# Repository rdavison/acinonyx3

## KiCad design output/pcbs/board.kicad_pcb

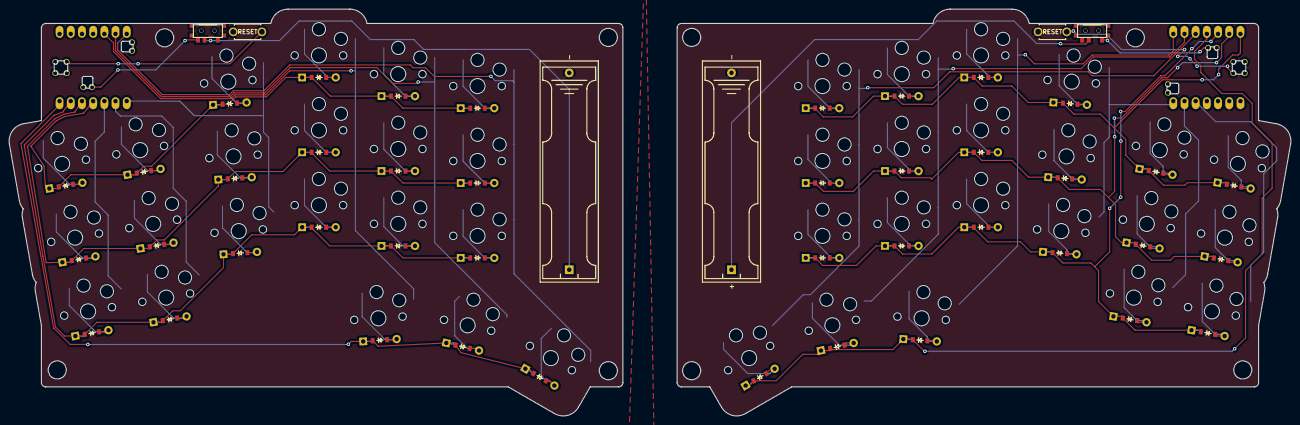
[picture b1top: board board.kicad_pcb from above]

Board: 2 copper layers, 290.9 x 92.3 mm, 92 parts (0 on the bottom side), 70 nets.

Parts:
AAAL: BatteryHolder_Keystone_2466_1xAAA
AAAR: BatteryHolder_Keystone_2466_1xAAA
B1, B2: ResetSW
D1, D2, D3, D4, D5, D6, D7, D8, D9, D10, D11, D12, D13, D14, D15, D16, D17, D18, D19, D20, D21, D22, D23, D24, D25, D26, D27, D28, D29, D30, D31, D32, D33, D34, D35, D36, D37, D38, D39, D40, D41, D42: ComboDiode
MCU1, MCU2: xiao-ble; XIAO-BLE
S1, S2, S3, S4, S5, S6, S7, S8, S9, S10, S11, S12, S13, S14, S15, S16, S17, S18, S19, S20, S21, S22, S23, S24, S25, S26, S27, S28, S29, S30, S31, S32, S33, S34, S35, S36, S37, S38, S39, S40, S41, S42: PG1350
T1, T2: SPDT_C128955

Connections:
BAT_POS: MCU1.19, T1.3
GND: AAAL.2, B1.2, MCU1.13, MCU1.17
RAW: AAAL.1, T1.2
RST: B1.1, MCU1.18
col_index: MCU1.9, S13.2, S14.2, S15.2, S20.2
col_inner: MCU1.8, S16.2, S17.2, S18.2, S21.2
col_middle: MCU1.10, S10.2, S11.2, S12.2, S19.2
col_outer: MCU1.5, S1.2, S2.2, S3.2
col_pinky: MCU1.6, S4.2, S5.2, S6.2
col_ring: MCU1.7, S7.2, S8.2, S9.2
far_thumb: D21.2, S21.1
home_thumb: D20.2, S20.1
index_bottom: D13.2, S13.1
index_home: D14.2, S14.1
index_top: D15.2, S15.1
inner_bottom: D16.2, S16.1
inner_home: D17.2, S17.1
inner_top: D18.2, S18.1
middle_bottom: D10.2, S10.1
middle_home: D11.2, S11.1
middle_top: D12.2, S12.1
mirror_BAT_POS: MCU2.19, T2.1
mirror_GND: AAAR.2, B2.2, MCU2.13, MCU2.17
mirror_RAW: AAAR.1, T2.2
mirror_RST: B2.1, MCU2.18
mirror_col_index: MCU2.6, S34.2, S35.2, S36.2, S41.2
mirror_col_inner: MCU2.5, S37.2, S38.2, S39.2, S42.2
mirror_col_middle: MCU2.7, S31.2, S32.2, S33.2, S40.2
mirror_col_outer: MCU2.10, S22.2, S23.2, S24.2
mirror_col_pinky: MCU2.9, S25.2, S26.2, S27.2
mirror_col_ring: MCU2.8, S28.2, S29.2, S30.2
mirror_far_thumb: D42.2, S42.1
mirror_home_thumb: D41.2, S41.1
mirror_index_bottom: D34.2, S34.1
mirror_index_home: D35.2, S35.1
mirror_index_top: D36.2, S36.1
mirror_inner_bottom: D37.2, S37.1
mirror_inner_home: D38.2, S38.1
mirror_inner_top: D39.2, S39.1
mirror_middle_bottom: D31.2, S31.1
mirror_middle_home: D32.2, S32.1
mirror_middle_top: D33.2, S33.1
mirror_near_thumb: D40.2, S40.1
mirror_outer_bottom: D22.2, S22.1
mirror_outer_home: D23.2, S23.1
mirror_outer_top: D24.2, S24.1
mirror_pinky_bottom: D25.2, S25.1
mirror_pinky_home: D26.2, S26.1
mirror_pinky_top: D27.2, S27.1
mirror_ring_bottom: D28.2, S28.1
mirror_ring_home: D29.2, S29.1
mirror_ring_top: D30.2, S30.1
mirror_row_bottom: D22.1, D25.1, D28.1, D31.1, D34.1, D37.1, MCU2.3
mirror_row_home: D23.1, D26.1, D29.1, D32.1, D35.1, D38.1, MCU2.2
mirror_row_thumb: D40.1, D41.1, D42.1, MCU2.4
mirror_row_top: D24.1, D27.1, D30.1, D33.1, D36.1, D39.1, MCU2.1
near_thumb: D19.2, S19.1
outer_bottom: D1.2, S1.1
outer_home: D2.2, S2.1
outer_top: D3.2, S3.1
pinky_bottom: D4.2, S4.1
pinky_home: D5.2, S5.1
pinky_top: D6.2, S6.1
ring_bottom: D7.2, S7.1
ring_home: D8.2, S8.1
ring_top: D9.2, S9.1
row_bottom: D1.1, D4.1, D7.1, D10.1, D13.1, D16.1, MCU1.2
row_home: D2.1, D5.1, D8.1, D11.1, D14.1, D17.1, MCU1.3
row_thumb: D19.1, D20.1, D21.1, MCU1.1
row_top: D3.1, D6.1, D9.1, D12.1, D15.1, D18.1, MCU1.4

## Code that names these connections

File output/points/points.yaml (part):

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                pinky: &ref_2
                    key:
                        stagger: 0 ky
                        column_net: col_pinky
                        mirror:
                            column_net: mirror_col_pinky
                    rows: {}
                    name: pinky
                ring: &ref_3
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        autobind: 10
        skip: false
        asym: both
        colrow: pinky_bottom
        name: matrix_pinky_bottom
        column_net: col_pinky
        mirror:
            column_net: mirror_col_pinky
            row_net: mirror_row_bottom
        row_net: row_bottom
        zone: *ref_1
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        autobind: 10
        skip: false
        asym: both
        colrow: pinky_home
        name: matrix_pinky_home
        column_net: col_pinky
        mirror:
            column_net: mirror_col_pinky
            row_net: mirror_row_home
        row_net: row_home
        zone: *ref_1
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        autobind: 10
        skip: false
        asym: both
        colrow: pinky_top
        name: matrix_pinky_top
        column_net: col_pinky
        mirror:
            column_net: mirror_col_pinky
            row_net: mirror_row_top
        row_net: row_top
        zone: *ref_1
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                pinky:
                    key:
                        stagger: 0 ky
                        column_net: col_pinky
                        mirror:
                            column_net: mirror_col_pinky
                    rows: {}
                    name: pinky
                ring:
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                pinky:
                    key:
                        stagger: 0 ky
                        column_net: col_pinky
                        mirror:
                            column_net: mirror_col_pinky
                    rows: {}
                    name: pinky
                ring:
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                pinky:
                    key:
                        stagger: 0 ky
                        column_net: col_pinky
                        mirror:
                            column_net: mirror_col_pinky
                    rows: {}
                    name: pinky
                ring:
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        autobind: 10
        skip: false
        asym: both
        colrow: mirror_pinky_bottom
        name: mirror_matrix_pinky_bottom
        column_net: mirror_col_pinky
        mirror:
            column_net: mirror_col_pinky
            row_net: mirror_row_bottom
        row_net: mirror_row_bottom
        zone:
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                pinky:
                    key:
                        stagger: 0 ky
                        column_net: col_pinky
                        mirror:
                            column_net: mirror_col_pinky
                    rows: {}
                    name: pinky
                ring:
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        col:
            key:
                stagger: 0 ky
                column_net: col_pinky
                mirror:
                    column_net: mirror_col_pinky
            rows: {}
            name: pinky
        row: bottom
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        autobind: 10
        skip: false
        asym: both
        colrow: mirror_pinky_home
        name: mirror_matrix_pinky_home
        column_net: mirror_col_pinky
        mirror:
            column_net: mirror_col_pinky
            row_net: mirror_row_home
        row_net: mirror_row_home
        zone:
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                pinky:
                    key:
                        stagger: 0 ky
                        column_net: col_pinky
                        mirror:
                            column_net: mirror_col_pinky
                    rows: {}
                    name: pinky
                ring:
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        col:
            key:
                stagger: 0 ky
                column_net: col_pinky
                mirror:
                    column_net: mirror_col_pinky
            rows: {}
            name: pinky
        row: home
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        autobind: 10
        skip: false
        asym: both
        colrow: mirror_pinky_top
        name: mirror_matrix_pinky_top
        column_net: mirror_col_pinky
        mirror:
            column_net: mirror_col_pinky
            row_net: mirror_row_top
        row_net: mirror_row_top
        zone:
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                pinky:
                    key:
                        stagger: 0 ky
                        column_net: col_pinky
                        mirror:
                            column_net: mirror_col_pinky
                    rows: {}
                    name: pinky
                ring:
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        col:
            key:
                stagger: 0 ky
                column_net: col_pinky
                mirror:
                    column_net: mirror_col_pinky
            rows: {}
            name: pinky
        row: top
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                pinky:
                    key:
                        stagger: 0 ky
                        column_net: col_pinky
                        mirror:
                            column_net: mirror_col_pinky
                    rows: {}
                    name: pinky
                ring:
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                pinky:
                    key:
                        stagger: 0 ky
                        column_net: col_pinky
                        mirror:
                            column_net: mirror_col_pinky
                    rows: {}
                    name: pinky
                ring:
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                pinky:
                    key:
                        stagger: 0 ky
                        column_net: col_pinky
                        mirror:
                            column_net: mirror_col_pinky
                    rows: {}
                    name: pinky
                ring:
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                pinky:
                    key:
                        stagger: 0 ky
                        column_net: col_pinky
                        mirror:
                            column_net: mirror_col_pinky
                    rows: {}
                    name: pinky
                ring:
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                pinky:
                    key:
                        stagger: 0 ky
                        column_net: col_pinky
                        mirror:
                            column_net: mirror_col_pinky
                    rows: {}
                    name: pinky
                ring:
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                pinky:
                    key:
                        stagger: 0 ky
                        column_net: col_pinky
                        mirror:
                            column_net: mirror_col_pinky
                    rows: {}
                    name: pinky
                ring:
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                pinky:
                    key:
                        stagger: 0 ky
                        column_net: col_pinky
                        mirror:
                            column_net: mirror_col_pinky
                    rows: {}
                    name: pinky
                ring:
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                pinky:
                    key:
                        stagger: 0 ky
                        column_net: col_pinky
                        mirror:
                            column_net: mirror_col_pinky
                    rows: {}
                    name: pinky
                ring:
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                pinky:
                    key:
                        stagger: 0 ky
                        column_net: col_pinky
                        mirror:
                            column_net: mirror_col_pinky
                    rows: {}
                    name: pinky
                ring:
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                pinky:
                    key:
                        stagger: 0 ky
                        column_net: col_pinky
                        mirror:
                            column_net: mirror_col_pinky
                    rows: {}
                    name: pinky
                ring:
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                pinky:
                    key:
                        stagger: 0 ky
                        column_net: col_pinky
                        mirror:
                            column_net: mirror_col_pinky
                    rows: {}
                    name: pinky
                ring:
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                pinky:
                    key:
                        stagger: 0 ky
                        column_net: col_pinky
                        mirror:
                            column_net: mirror_col_pinky
                    rows: {}
                    name: pinky
                ring:
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
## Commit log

2023-11-20 Set maximum batch autorouter passes to 64
2023-11-23 Use my own fork of ergogen
2023-11-23 Revert "Use my own fork of ergogen"
    This reverts commit f5cf76b4b557727d7415b73efa77ffb1f28604f0.
2023-11-23 Fix plate
2023-11-25 MX version
2023-11-26 xiao
2023-11-26 mcu_r
2023-11-26 Update lockfile
2023-11-27 checkpoint
2023-11-27 change footprint to module
2024-01-31 dgaf, adding a number row
